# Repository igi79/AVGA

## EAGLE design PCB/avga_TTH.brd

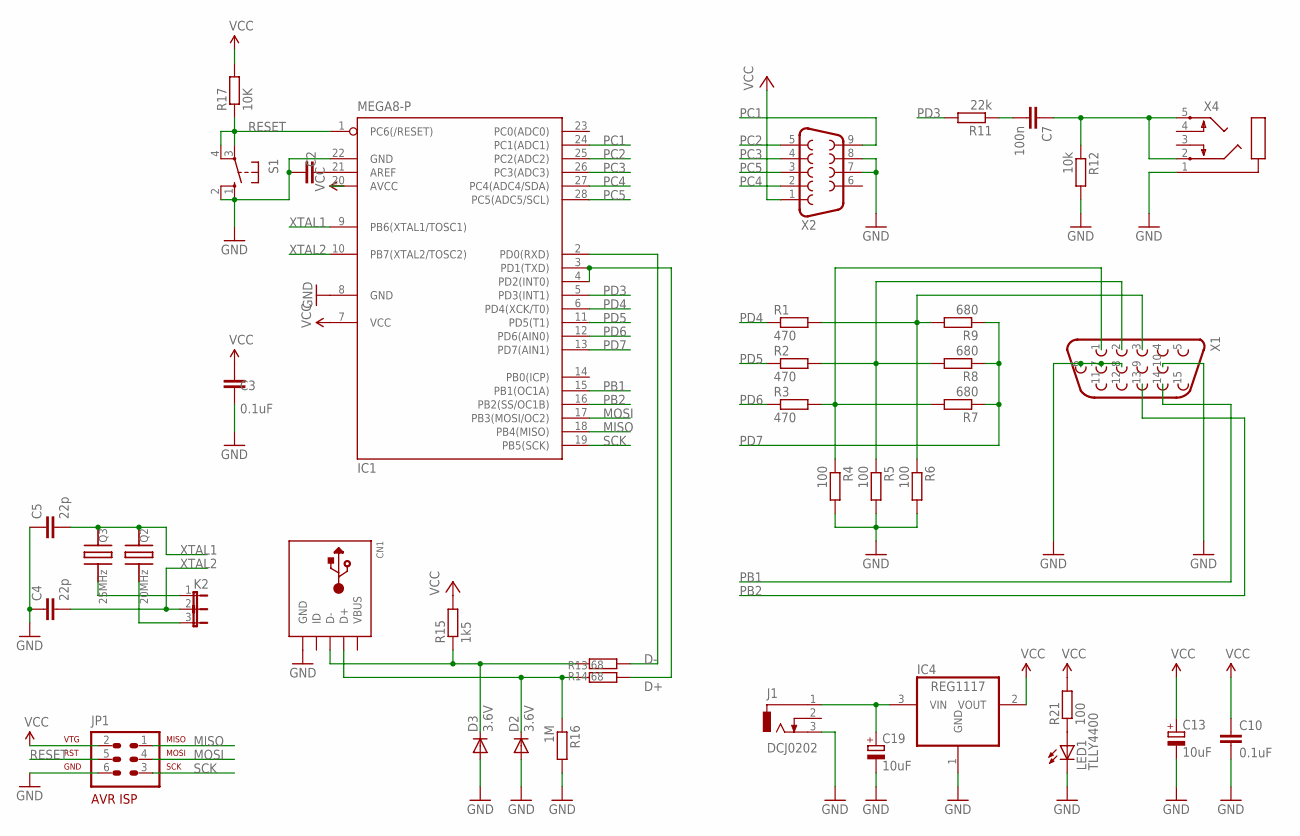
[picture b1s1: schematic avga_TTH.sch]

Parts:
C2, C3, C10: 0.1uF; C0805
C4, C5: 22p; C0805
C7: 100n; C0805
C13, C19: 10uF; E2,5-5
CN1: USBMINIB; USB-MINIB
D2, D3: 3.6V; MINIMELF
IC1: MEGA8-P; DIL28-3
IC4: REG1117; SOT223
J1: DCJ0202
JP1: AVR-ISP-6R
K2: CON-3-POL; MOLEX-PSK-03
LED1: TLLY4400; LED3MM
Q2: 20MHz; QUARZ
Q3: 25MHz; QUARZ
R1, R2, R3: 470; R0805
R4, R5, R6, R21: 100; R0805
R7, R8, R9: 680; R0805
R11: 22k; R0805
R12: 10k; R0805
R13, R14: 68; R0805
R15: 1k5; R0805
R16: 1M; R0805
R17: 10K; R0805
S1: 10-XX; B3F-10XX
X1: VGA-BU-15POL
X2: M09HP
X4: KLINKENBUCHSE

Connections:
B: R1.2, R6.1, R9.2, X1.3
G: R2.2, R5.1, R8.2, X1.2
GND: C2.2, C3.1, C4.1, C5.1, C10.2, C13.-, C19.-, CN1.GND, D2.A, D3.A, IC1.8 (GND), IC1.22 (GND), IC4.1 (GND), J1.3, JP1.6, LED1.K (C), R4.2, R5.2, R6.2, R12.2, R16.2, S1.1 (S), S1.2 (S1), X1.6, X1.7, X1.8, X1.10, X2.7, X2.8, X4.1
MISO: IC1.18 (PB4(MISO)), JP1.1
MOSI: IC1.17 (PB3(MOSI/OC2)), JP1.4
unnamed: LED1.A, R21.1
unnamed: C7.1, R12.1, X4.2, X4.5
unnamed: K2.1, Q3.2
unnamed: CN1.D+, D2.C, R13.1, R16.1
unnamed: CN1.D-, D3.C, R14.1, R15.1
unnamed: C7.2, R11.1
unnamed: IC1.3 (PD1(TXD)), IC1.4 (PD2(INT0)), R13.2
unnamed: IC1.2 (PD0(RXD)), R14.2
unnamed: K2.3, Q2.2
unnamed: C2.1, IC1.21 (AREF)
PB1: IC1.15 (PB1(OC1A)), X1.14
PB2: IC1.16 (PB2(SS/OC1B)), X1.13
PC1: IC1.24 (PC1(ADC1)), X2.9
PC2: IC1.25 (PC2(ADC2)), X2.5
PC3: IC1.26 (PC3(ADC3)), X2.4
PC4: IC1.27 (PC4(ADC4/SDA)), X2.2
PC5: IC1.28 (PC5(ADC5/SCL)), X2.3
PD3: IC1.5 (PD3(INT1)), R11.2
PD4: IC1.6 (PD4(XCK/T0)), R1.1
PD5: IC1.11 (PD5(T1)), R2.1
PD6: IC1.12 (PD6(AIN0)), R3.1
PD7: IC1.13 (PD7(AIN1)), R7.1, R8.1, R9.1
R: R3.2, R4.1, R7.2, X1.1
RESET: IC1.1 (PC6(/RESET)), JP1.5, R17.1, S1.3, S1.4 (P1)
SCK: IC1.19 (PB5(SCK)), JP1.3
VBUS: CN1.VBUS
VCC: C3.2, C10.1, C13.+, IC1.7 (VCC), IC1.20 (AVCC), IC4.2 (VOUT), JP1.2, R15.2, R17.2, R21.2, X2.1
VIN: C19.+, IC4.3 (VIN), J1.1
XTAL1: C5.2, IC1.9 (PB6(XTAL1/TOSC1)), Q2.1, Q3.1
XTAL2: C4.2, IC1.10 (PB7(XTAL2/TOSC2)), K2.2

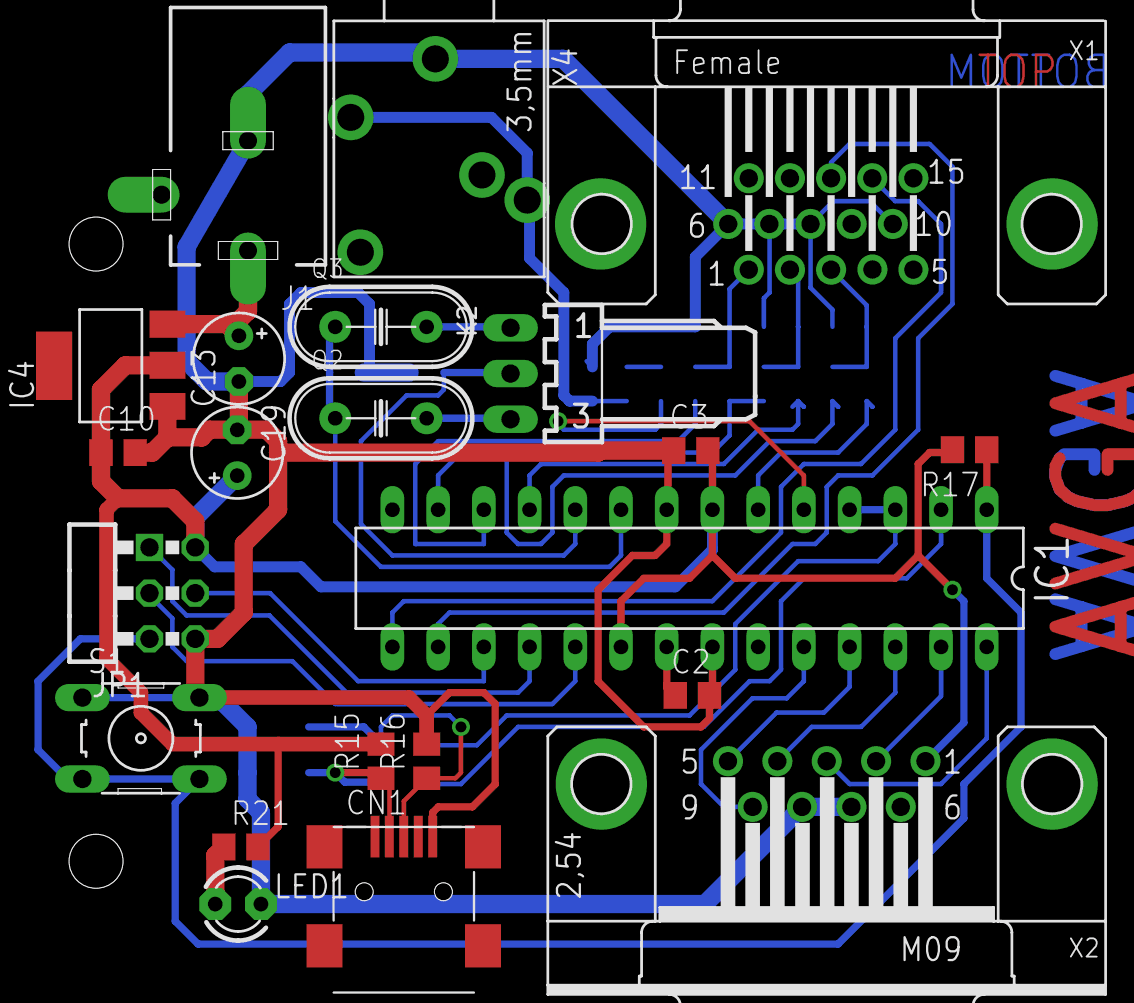
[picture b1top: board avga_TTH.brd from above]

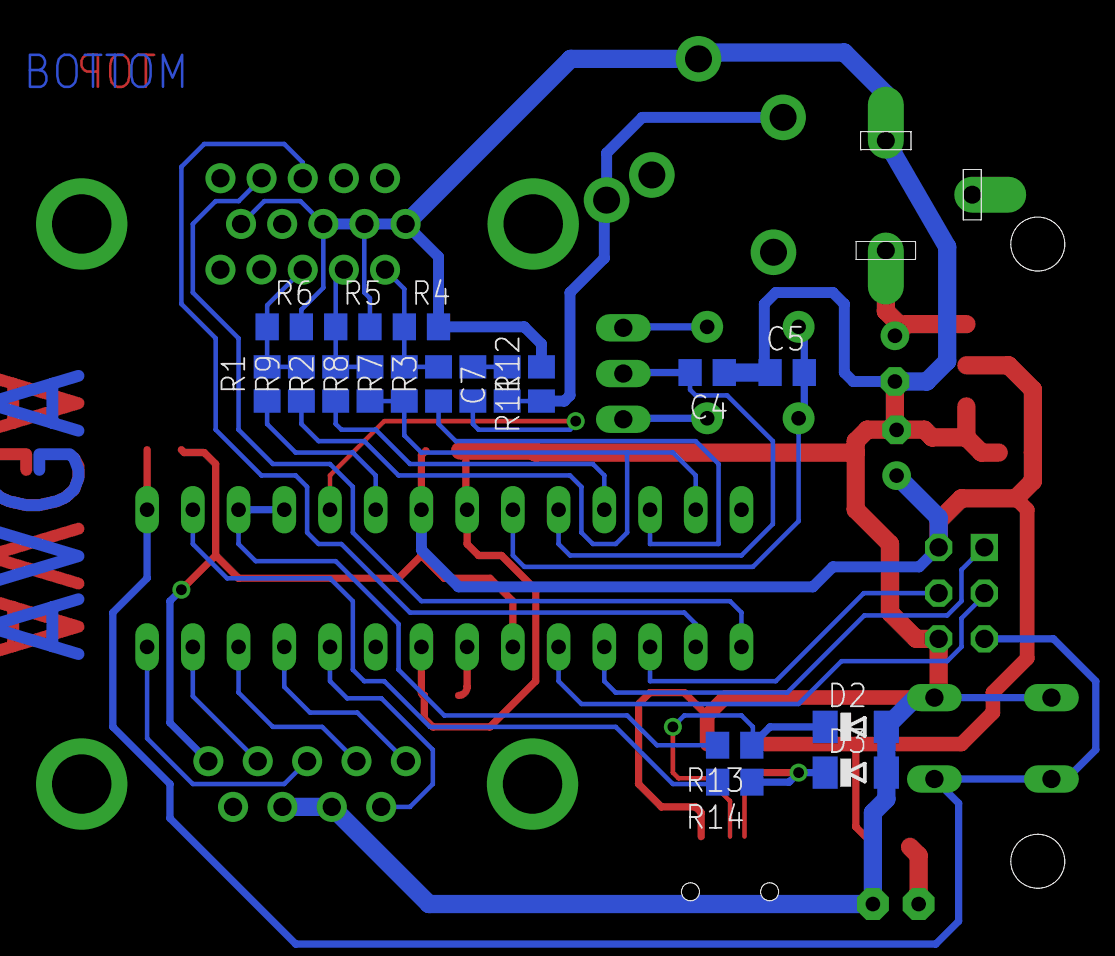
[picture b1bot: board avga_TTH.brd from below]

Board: 2 copper layers, 40 parts (18 on the bottom side), 34 nets.

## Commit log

2016-03-15 avga final
2016-03-19 Imgs
2016-03-20 Through the hole (TTH) component version
2016-03-20 PCB in PDF
